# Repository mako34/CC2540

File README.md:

Brake out board for TI  CC2540

test one on Trough hole tech, 
to come smd

better layout

.)

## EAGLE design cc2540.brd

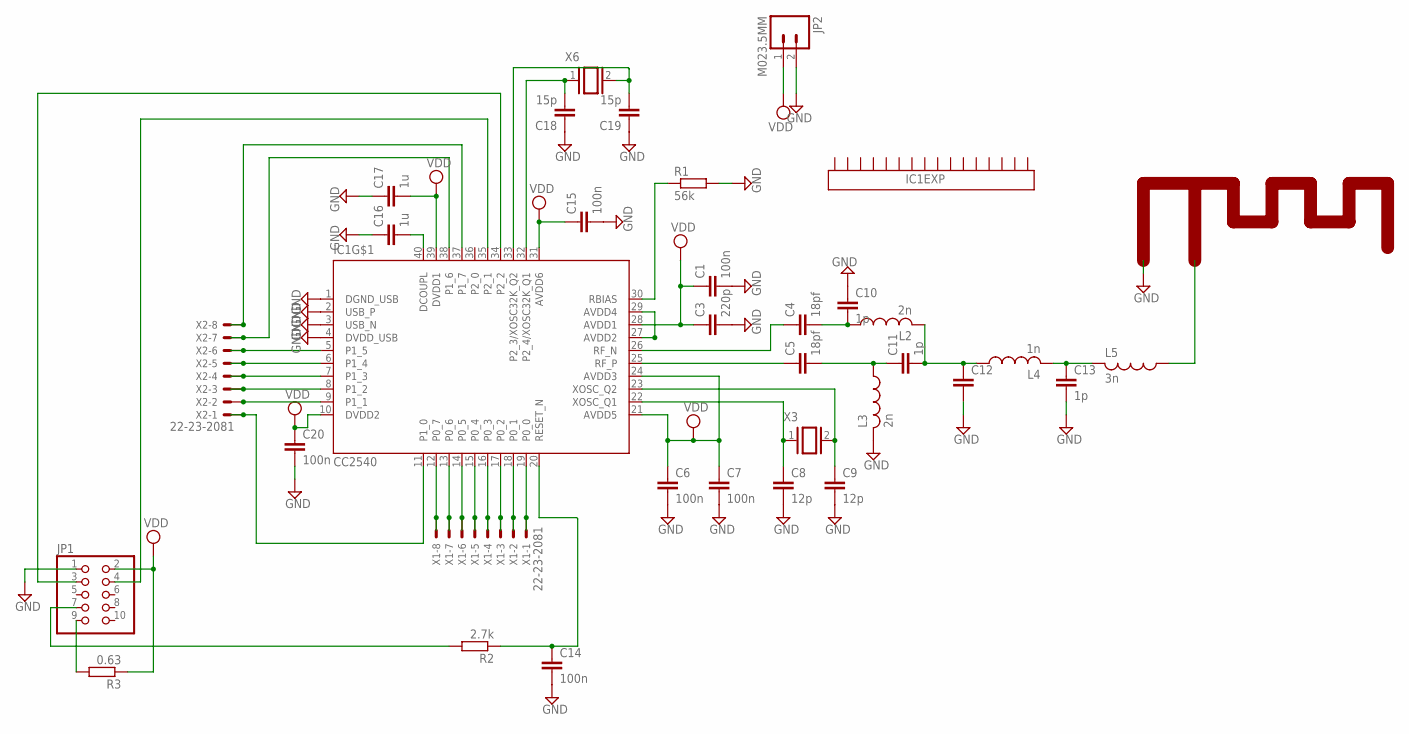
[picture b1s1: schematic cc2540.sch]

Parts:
A1: TI_2.4GHZ_MIFALEFT; TI_2.4GHZ_MIFA_LEFT
C1, C6, C7, C14, C15, C20: 100n; C025-025X050
C3: 220p; C025-025X050
C4, C5: 18pf; C025-025X050
C8, C9: 12p; C025-025X050
C10, C11, C13: 1p; C025-025X050
C12: C-EU025-025X050; C025-025X050
C16, C17: 1u; C025-025X050
C18, C19: 15p; C025-025X050
IC1: CC2540; QFN40-6X6
JP1: PINHD-2X51.27_SMD; 2X05_1.27_SMD
JP2: M023.5MM; SCREWTERMINAL-3.5MM-2
L2, L3: 2n; 0204/5
L4: 1n; 0204/5
L5: 3n; 0204/5
R1: 56k; 0204V
R2: 2.7k; 0204V
R3: 0.63; 0204V
X1, X2: 22-23-2081
X3, X6: XTAL/S; QS

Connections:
GND: A1.GND, C1.2, C3.2, C6.2, C7.2, C8.2, C9.2, C10.1, C12.2, C13.2, C14.2, C15.2, C16.1, C17.1, C18.1, C19.1, C20.2, IC1.1 (DGND_USB), IC1.2 (USB_P), IC1.3 (USB_N), IC1.4 (DVDD_USB), JP1.1, JP2.2, L3.2, R1.2
unnamed: IC1.30 (RBIAS), R1.1
unnamed: C4.1, IC1.26 (RF_N)
unnamed: C5.1, IC1.25 (RF_P)
unnamed: C8.1, IC1.22 (XOSC_Q1), X3.1
unnamed: C9.1, IC1.23 (XOSC_Q2), X3.2
unnamed: C4.2, C10.2, L2.1
unnamed: C5.2, C11.1, L3.1
unnamed: C11.2, C12.1, L2.2, L4.1
unnamed: C13.1, L4.2, L5.2
unnamed: IC1.19 (P0_0), X1.1
unnamed: IC1.18 (P0_1), X1.2
unnamed: IC1.17 (P0_2), X1.3
unnamed: IC1.16 (P0_3), X1.4
unnamed: IC1.15 (P0_4), X1.5
unnamed: IC1.14 (P0_5), X1.6
unnamed: IC1.13 (P0_6), X1.7
unnamed: IC1.12 (P0_7), X1.8
unnamed: IC1.27 (AVDD2), IC1.29 (AVDD4)
unnamed: IC1.9 (P1_1), X2.2
unnamed: IC1.8 (P1_2), X2.3
unnamed: IC1.7 (P1_3), X2.4
unnamed: IC1.6 (P1_4), X2.5
unnamed: IC1.5 (P1_5), X2.6
unnamed: IC1.38 (P1_6), X2.7
unnamed: C19.2, IC1.33 (P2_3/XOSC32K_Q2), X6.2
unnamed: C18.2, IC1.32 (P2_4/XOSC32K_Q1), X6.1
unnamed: C14.1, IC1.20 (RESET_N), R2.1
unnamed: IC1.37 (P1_7), X2.8
unnamed: C16.2, IC1.40 (DCOUPL)
unnamed: A1.FEED, L5.1
unnamed: JP1.7, R2.2
unnamed: JP1.9, R3.2
unnamed: IC1.34 (P2_2), JP1.3
unnamed: IC1.35 (P2_1), JP1.4
unnamed: IC1.11 (P1_0), X2.1
VDD: C1.1, C3.1, C6.1, C7.1, C15.1, C17.2, C20.1, IC1.10 (DVDD2), IC1.21 (AVDD5), IC1.24 (AVDD3), IC1.28 (AVDD1), IC1.31 (AVDD6), IC1.39 (DVDD1), JP1.2, JP2.1, R3.1

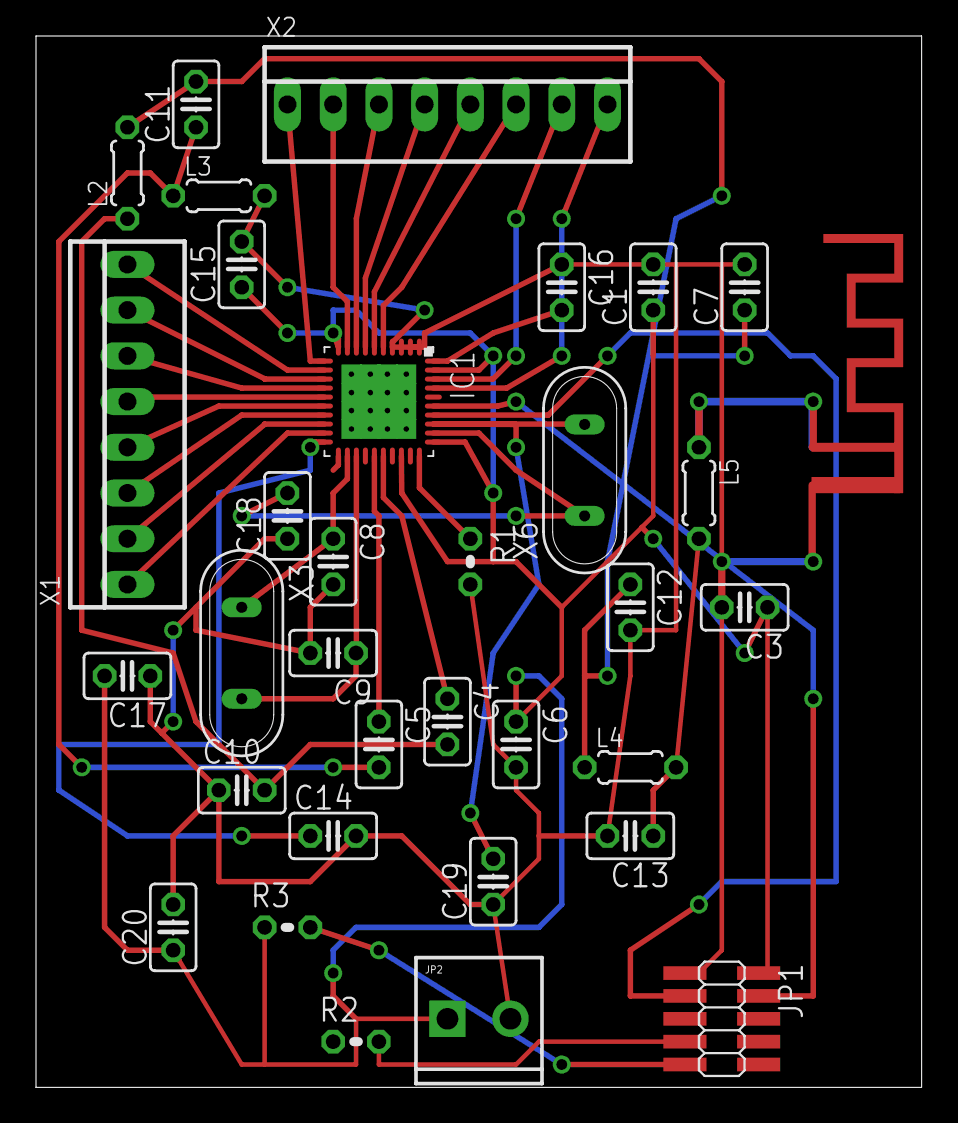
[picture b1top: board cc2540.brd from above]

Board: 2 copper layers, 49.2 x 58.4 mm, 34 parts (0 on the bottom side), 37 nets.

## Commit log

2013-09-19 break out board project started GIT
2013-09-20 clean version files

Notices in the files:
parts and their libraries:
SparkFun-Connectors: Licensing: CC v3.0 Share-Alike You are welcome to use this library for commercial purposes.
